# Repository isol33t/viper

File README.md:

# Duck Viper v1 PCB - Open Source Upgrade

⚠️ **Work in Progress** - This project is currently under development

Inspired by [Automated keyboard PCB design with ergogen and kbplacer by adamws](https://adamws.github.io/keyboard-pcb-design-with-ergogen-and-kbplacer/) & its [dockerfile](https://github.com/adamws/kicad-kbplacer/blob/develop/examples/absolem-ergogen/Dockerfile).

<!-- 

 -->

## Overview

An open-source PCB design for the Duck Viper v1 keyboard with hardware upgrades. This project focuses on transparency and community collaboration while building upon existing open-source resources.

**Disclaimer:** I'm not an electrical engineer - this project represents my attempt at "putting the parts together" using available community resources, guides, and libraries. Community feedback and contributions are greatly appreciated!

(Planned *) Upgrades: 
- USB-C Connector
- ESD
- Separate Caps Lock LED
- - RGB Underglow *
- - Additional switches for Split HHKB Bottom Row *
- - MXLockLed *

## Design Philosophy

- **Open Source First**: All design files, schematics, and documentation will be freely available
- **Community Driven**: Built using existing open-source libraries and community knowledge
- **Transparency**: Design decisions and trade-offs documented for others to learn from

## Current Status

[Link to PDF](hardware/schematic.pdf)

### Design Questions (Help Needed!)

**1. QFN vs QFP Package Decision**
- **QFN Pros**: Required for split HHKB layout with IC positioned between Caps Lock and A (see Voyager60 reference)
- **QFN Cons**: Hand soldering difficulty increases prototype cost (~$20 per PCB for 5-unit orders with just an assembled QFN IC vs ~$10 for 5 PCBs ex. assembly)
- **QFP**: Easier to hand solder but may not fit desired layout constraints due to additional stabilizer requirements for split HHKB

QFN IC placement mock-up:

*If going QFN route, schematic verification help would be greatly appreciated!*

## Supported Layouts

kbplacer can use via for switch placement & requires via for collapsing a KLE layout

VIA spec https://www.caniusevia.com/docs/layouts#overview uses KLE raw, but not kle.com's raw json
VIA spec based on [wt60_d](https://github.com/the-via/keyboards/blob/9da730d66a00c3ca1b9b9ac7e7078fc221432501/v3/wilba_tech/wt60_d/wt60_d.json#L9)

```
python -m kbplacer.kle_serial -in -in kle/keyboard-layout-via-10u.json -inform KLE_VIA -out keyboard-layout-collapsed.json -outform KLE_RAW -collapse
```

- Forked [duck_viper](https://adamws.github.io/keyboard-pcbs/#duck-eagle_viper-v2-eagle_viper)

### Split HHKB, 10u

[KLE permalink](https://keyboard-layout-editor.com/##@@_x:2&c=%23777777%3B&=0,0&_c=%23cccccc%3B&=0,1&=0,2&=0,3&=0,4&=0,5&=0,6&=0,7&=0,8&=0,9&=0,10&=0,11&=0,12&_c=%23aaaaaa&w:2%3B&=0,13%0A%0A%0A0,0&_x:1.5&c=%23cccccc%3B&=0,13%0A%0A%0A0,1&=0,14%0A%0A%0A0,1%3B&@_x:2&c=%23aaaaaa&w:1.5%3B&=1,0&_c=%23cccccc%3B&=1,1&=1,2&=1,3&=1,4&=1,5&=1,6&=1,7&=1,8&=1,9&=1,10&=1,11&=1,12&_w:1.5%3B&=1,13%3B&@_c=%23aaaaaa&w:1.25%3B&=2,0%0A%0A%0A3,1&_x:0.75&w:1.75%3B&=2,0%0A%0A%0A3,0&_c=%23cccccc%3B&=2,1&=2,2&=2,3&=2,4&=2,5&=2,6&=2,7&=2,8&=2,9&=2,10&=2,11&_c=%23777777&w:2.25%3B&=2,12%3B&@_x:2&c=%23aaaaaa&w:2.25%3B&=3,1&_c=%23cccccc%3B&=3,2&=3,3&=3,4&=3,5&=3,6&=3,7&=3,8&=3,9&=3,10&=3,11&_c=%23aaaaaa&w:2.75%3B&=3,12%0A%0A%0A1,0&_x:0.75&w:1.75%3B&=3,12%0A%0A%0A1,1&=3,13%0A%0A%0A1,1%3B&@_x:2&w:1.5&d:true%3B&=4,0%0A%0A%0A2,0&=4,2%0A%0A%0A2,0&_w:1.5%3B&=4,3%0A%0A%0A2,0&_c=%23cccccc&w:7%3B&=4,7%0A%0A%0A2,0&_c=%23aaaaaa&w:1.5%3B&=4,11%0A%0A%0A2,0&=4,13%0A%0A%0A2,0&_w:1.5&d:true%3B&=4,14%0A%0A%0A2,0%3B&@_x:2&y:0.5&w:1.5&d:true%3B&=4,0%0A%0A%0A2,1&=4,2%0A%0A%0A2,1&_w:1.5%3B&=4,3%0A%0A%0A2,1&_c=%23cccccc&w:3%3B&=4,5%0A%0A%0A2,1&=4,7%0A%0A%0A2,1&_w:3%3B&=4,9%0A%0A%0A2,1&_c=%23aaaaaa&w:1.5%3B&=4,11%0A%0A%0A2,1&=4,13%0A%0A%0A2,1&_w:1.5&d:true%3B&=4,14%0A%0A%0A2,1%3B&@_x:2&w:1.5&d:true%3B&=4,0%0A%0A%0A2,2&=4,2%0A%0A%0A2,2&_c=%23cccccc&w:10%3B&=4,7%0A%0A%0A2,2&_c=%23aaaaaa%3B&=4,13%0A%0A%0A2,2&_w:1.5&d:true%3B&=4,14%0A%0A%0A2,2)

<details>
<summary>KLE Raw data, expanded</summary>
```
[{"x": 2, "c": "#777777"}, "0,0", {"c": "#cccccc"}, "0,1", "0,2", "0,3", "0,4", "0,5", "0,6", "0,7", "0,8", "0,9", "0,10", "0,11", "0,12", {"c": "#aaaaaa", "w": 2}, "0,13\n\n\n0,0", {"x": 1.5, "c": "#cccccc"}, "0,13\n\n\n0,1", "0,14\n\n\n0,1"],
[{"x": 2, "c": "#aaaaaa", "w": 1.5}, "1,0", {"c": "#cccccc"}, "1,1", "1,2", "1,3", "1,4", "1,5", "1,6", "1,7", "1,8", "1,9", "1,10", "1,11", "1,12", {"w": 1.5}, "1,13"],
[{"c": "#aaaaaa", "w": 1.25}, "2,0\n\n\n3,1", {"x": 0.75, "w": 1.75}, "2,0\n\n\n3,0", {"c": "#cccccc"}, "2,1", "2,2", "2,3", "2,4", "2,5", "2,6", "2,7", "2,8", "2,9", "2,10", "2,11", {"c": "#777777", "w": 2.25}, "2,12"],
[{"x": 2, "c": "#aaaaaa", "w": 2.25}, "3,1", {"c": "#cccccc"}, "3,2", "3,3", "3,4", "3,5", "3,6", "3,7", "3,8", "3,9", "3,10", "3,11", {"c": "#aaaaaa", "w": 2.75}, "3,12\n\n\n1,0", {"x": 0.75, "w": 1.75}, "3,12\n\n\n1,1", "3,13\n\n\n1,1"],
[{"x": 2, "w": 1.5, "d": true}, "4,0\n\n\n2,0", "4,2\n\n\n2,0", {"w": 1.5}, "4,3\n\n\n2,0", {"c": "#cccccc", "w": 7}, "4,7\n\n\n2,0", {"c": "#aaaaaa", "w": 1.5}, "4,11\n\n\n2,0", "4,13\n\n\n2,0", {"w": 1.5, "d": true}, "4,14\n\n\n2,0"],
[{"x": 2, "y": 0.5, "w": 1.5, "d": true}, "4,0\n\n\n2,1", "4,2\n\n\n2,1", {"w": 1.5}, "4,3\n\n\n2,1", {"c": "#cccccc", "w": 3}, "4,5\n\n\n2,1", "4,7\n\n\n2,1", {"w": 3}, "4,9\n\n\n2,1", {"c": "#aaaaaa", "w": 1.5}, "4,11\n\n\n2,1", "4,13\n\n\n2,1", {"w": 1.5, "d": true}, "4,14\n\n\n2,1"],
[{"x": 2, "w": 1.5, "d": true}, "4,0\n\n\n2,2", "4,2\n\n\n2,2", {"c": "#cccccc", "w": 10}, "4,7\n\n\n2,2", {"c": "#aaaaaa"}, "4,13\n\n\n2,2", {"w": 1.5, "d": true}, "4,14\n\n\n2,2"]
```
</details>

[KLE permalink](https://keyboard-layout-editor.com/##@@_x:2&c=%23777777%3B&=0,0&_c=%23cccccc%3B&=0,1&=0,2&=0,3&=0,4&=0,5&=0,6&=0,7&=0,8&=0,9&=0,10&=0,11&=0,12&_c=%23aaaaaa&w:2%3B&=0,13%0A%0A%0A0,0&_x:-2&c=%23cccccc%3B&=0,13%0A%0A%0A0,1&=0,14%0A%0A%0A0,1%3B&@_x:2&c=%23aaaaaa&w:1.5%3B&=1,0&_c=%23cccccc%3B&=1,1&=1,2&=1,3&=1,4&=1,5&=1,6&=1,7&=1,8&=1,9&=1,10&=1,11&=1,12&_w:1.5%3B&=1,13%3B&@_x:2&c=%23aaaaaa&w:1.75%3B&=2,0%0A%0A%0A3,0&_x:-1.75&w:1.25%3B&=2,0%0A%0A%0A3,1&_x:0.5&c=%23cccccc%3B&=2,1&=2,2&=2,3&=2,4&=2,5&=2,6&=2,7&=2,8&=2,9&=2,10&=2,11&_c=%23777777&w:2.25%3B&=2,12%3B&@_x:2&c=%23aaaaaa&w:2.25%3B&=3,1&_c=%23cccccc%3B&=3,2&=3,3&=3,4&=3,5&=3,6&=3,7&=3,8&=3,9&=3,10&=3,11&_c=%23aaaaaa&w:2.75%3B&=3,12%0A%0A%0A1,0&_x:-2.75&w:1.75%3B&=3,12%0A%0A%0A1,1&=3,13%0A%0A%0A1,1%3B&@_x:3.5%3B&=4,2%0A%0A%0A2,0&_w:1.5%3B&=4,3%0A%0A%0A2,0&_c=%23cccccc&w:3%3B&=4,5%0A%0A%0A2,1&_x:-3&w:7%3B&=4,7%0A%0A%0A2,0&_x:-3&w:3%3B&=4,9%0A%0A%0A2,1&_c=%23aaaaaa&w:1.5%3B&=4,11%0A%0A%0A2,0&=4,13%0A%0A%0A2,0)

<details>
<summary>KLE Raw data, collapsed</summary>
```
[{"x": 2, "c": "#777777"}, "0,0", {"c": "#cccccc"}, "0,1", "0,2", "0,3", "0,4", "0,5", "0,6", "0,7", "0,8", "0,9", "0,10", "0,11", "0,12", {"c": "#aaaaaa", "w": 2}, "0,13\n\n\n0,0", {"x": -2, "c": "#cccccc"}, "0,13\n\n\n0,1", "0,14\n\n\n0,1"],
[{"x": 2, "c": "#aaaaaa", "w": 1.5}, "1,0", {"c": "#cccccc"}, "1,1", "1,2", "1,3", "1,4", "1,5", "1,6", "1,7", "1,8", "1,9", "1,10", "1,11", "1,12", {"w": 1.5}, "1,13"],
[{"x": 2.0, "c": "#aaaaaa", "w": 1.75}, "2,0\n\n\n3,0", {"x": -1.75, "w": 1.25}, "2,0\n\n\n3,1", {"x": 0.5, "c": "#cccccc"}, "2,1", "2,2", "2,3", "2,4", "2,5", "2,6", "2,7", "2,8", "2,9", "2,10", "2,11", {"c": "#777777", "w": 2.25}, "2,12"],
[{"x": 2, "c": "#aaaaaa", "w": 2.25}, "3,1", {"c": "#cccccc"}, "3,2", "3,3", "3,4", "3,5", "3,6", "3,7", "3,8", "3,9", "3,10", "3,11", {"c": "#aaaaaa", "w": 2.75}, "3,12\n\n\n1,0", {"x": -2.75, "w": 1.75}, "3,12\n\n\n1,1", "3,13\n\n\n1,1"],
[{"x": 3.5}, "4,2\n\n\n2,0", {"w": 1.5}, "4,3\n\n\n2,0", {"c": "#cccccc", "w": 3}, "4,5\n\n\n2,1", {"x": -3.0, "w": 7}, "4,7\n\n\n2,0", {"x": -3.0, "w": 3}, "4,9\n\n\n2,1", {"c": "#aaaaaa", "w": 1.5}, "4,11\n\n\n2,0", "4,13\n\n\n2,0"]
```
</details>

## Development Environment Setup

### Hardware Design (KiCad)

**Requirements:**
- KiCad 9.0 or later
- Git for version control
- - python3
- - docker

**Setup:**
```bash
# Clone the repository
git clone [repository-url]
cd duck-viper-v1-pcb

# Open the project in KiCad
# File -> Open Project -> duck-viper-v1.kicad_pro
```

**Setup for adamws/kbplacer:**
```bash
# Clone the repository
git clone [repository-url]
cd duck-viper-v1-pcb
python3 -m venv .venv
source .venv/bin/activate
python3 -m pip install .

python -m kbplacer.kle_serial -in kle/keyboard-layout-via.json -inform KLE_VIA -out kle/keyboard-layout-collapsed.json -outform KLE_INTERNAL -collapse
python tools/layout2url.py -in keyboard-layout-collapsed.json|pbcopy

# Open the project in KiCad
# File -> Open Project -> duck-viper-v1.kicad_pro
```

**linux**
```bash
python3 -m venv .venv --system-site-packages
source .venv/bin/activate
pip install .

# test kicad
python -c "import pcbnew; print(pcbnew.Version())"
```

**Libraries Used:**
- [AcheronProject/AlexandriaLibrary](https://github.com/AcheronProject/AlexandriaLibrary)
- Community keyboard libraries (specific sources TBD)

### Firmware Development

*Detailed firmware setup instructions will be added as development progresses.*

### Manufacturing Files

Generation of Gerber files, pick-and-place files, and BOM will be documented once design is finalized.

## Acknowledgments

This project builds upon the incredible work of the open-source keyboard community. Specific libraries, guides, and resources used will be documented as the project progresses.

## Contributing

As a learning project, I welcome:
- Schematic reviews and feedback
- Design suggestions and improvements
- Documentation contributions
- Testing and validation help

## Thanks yo

This project is inspired by [Automated Keyboard PCB design with ergogen and kbplacer](https://github.com/adamws/kicad-kbplacer/tree/master/examples/absolem-ergogen). Still, it's far from being fully automated.

- adamws/kicad-kbplacer
- https://github.com/ruiqimao/keyboard-pcb-guide
- https://wiki.ai03.com/books/pcb-design
- https://github.com/evyd13/plain60-b
- https://github.com/evyd13/plain60-c
- https://www.masterzen.fr/2020/05/03/designing-a-keyboard-part-1/

## License

[MIT](LICENSE)

---

*This project is a learning exercise in PCB design. Use at your own risk and always verify designs before manufacturing.*

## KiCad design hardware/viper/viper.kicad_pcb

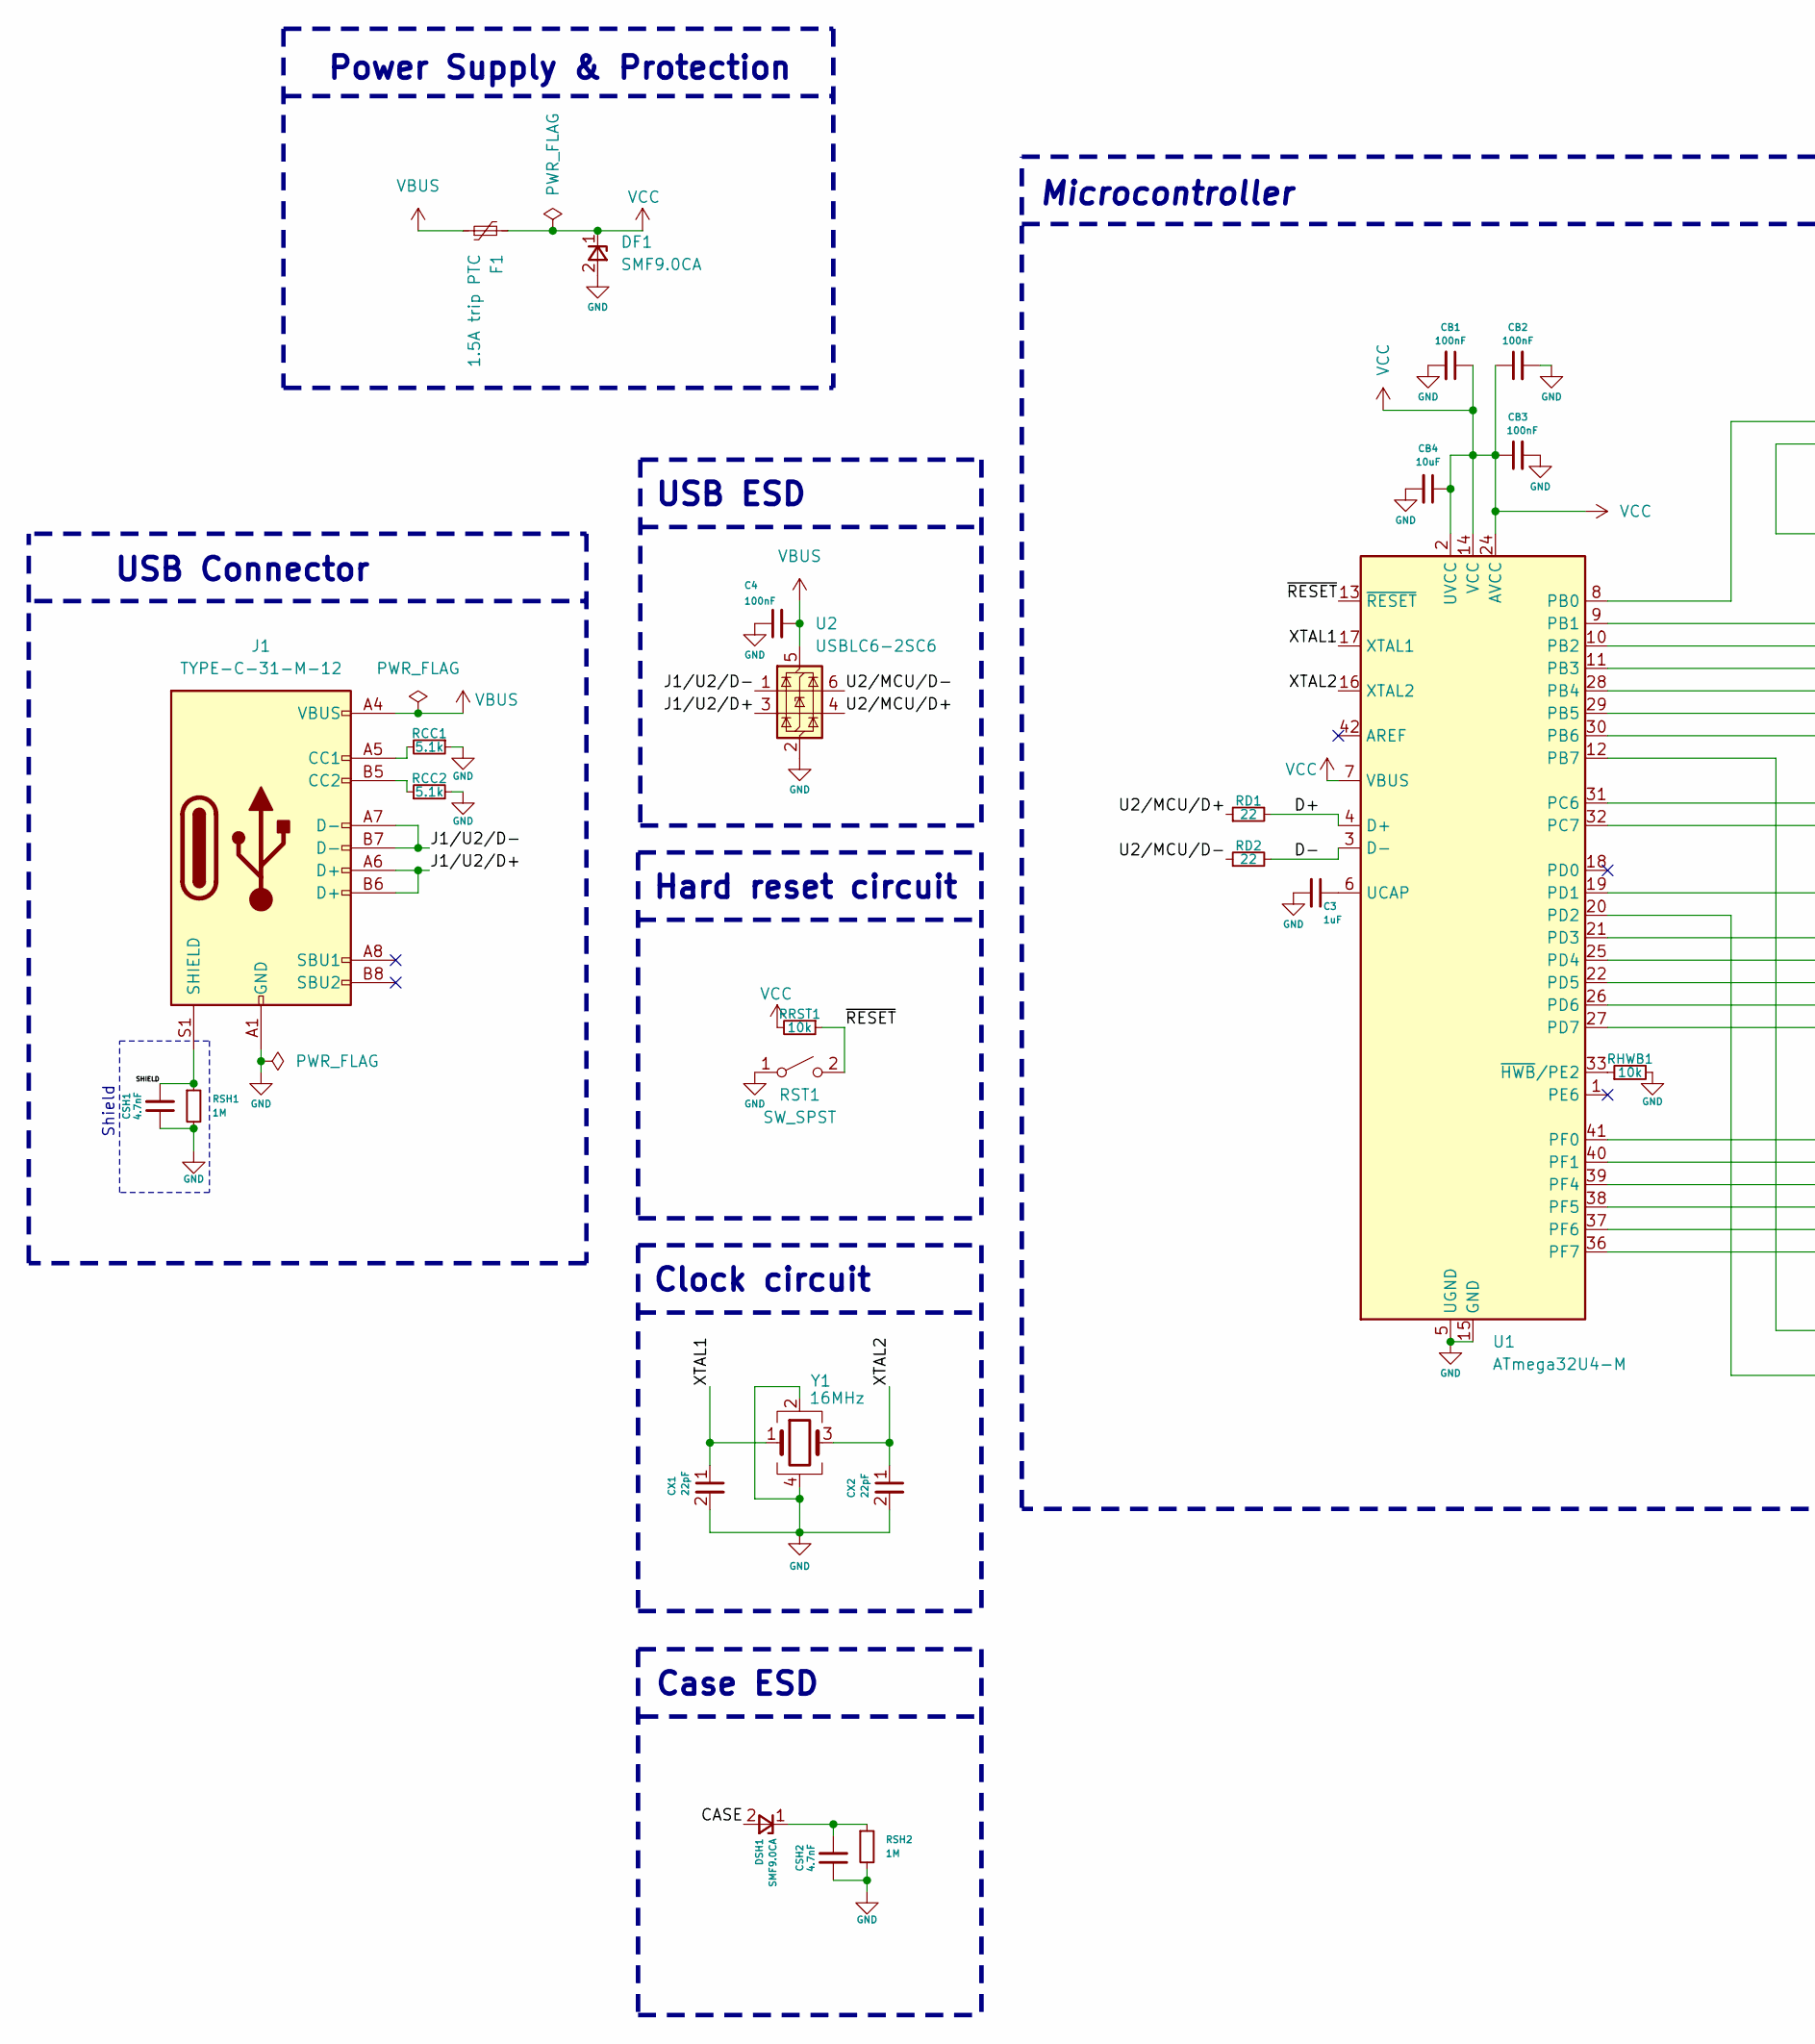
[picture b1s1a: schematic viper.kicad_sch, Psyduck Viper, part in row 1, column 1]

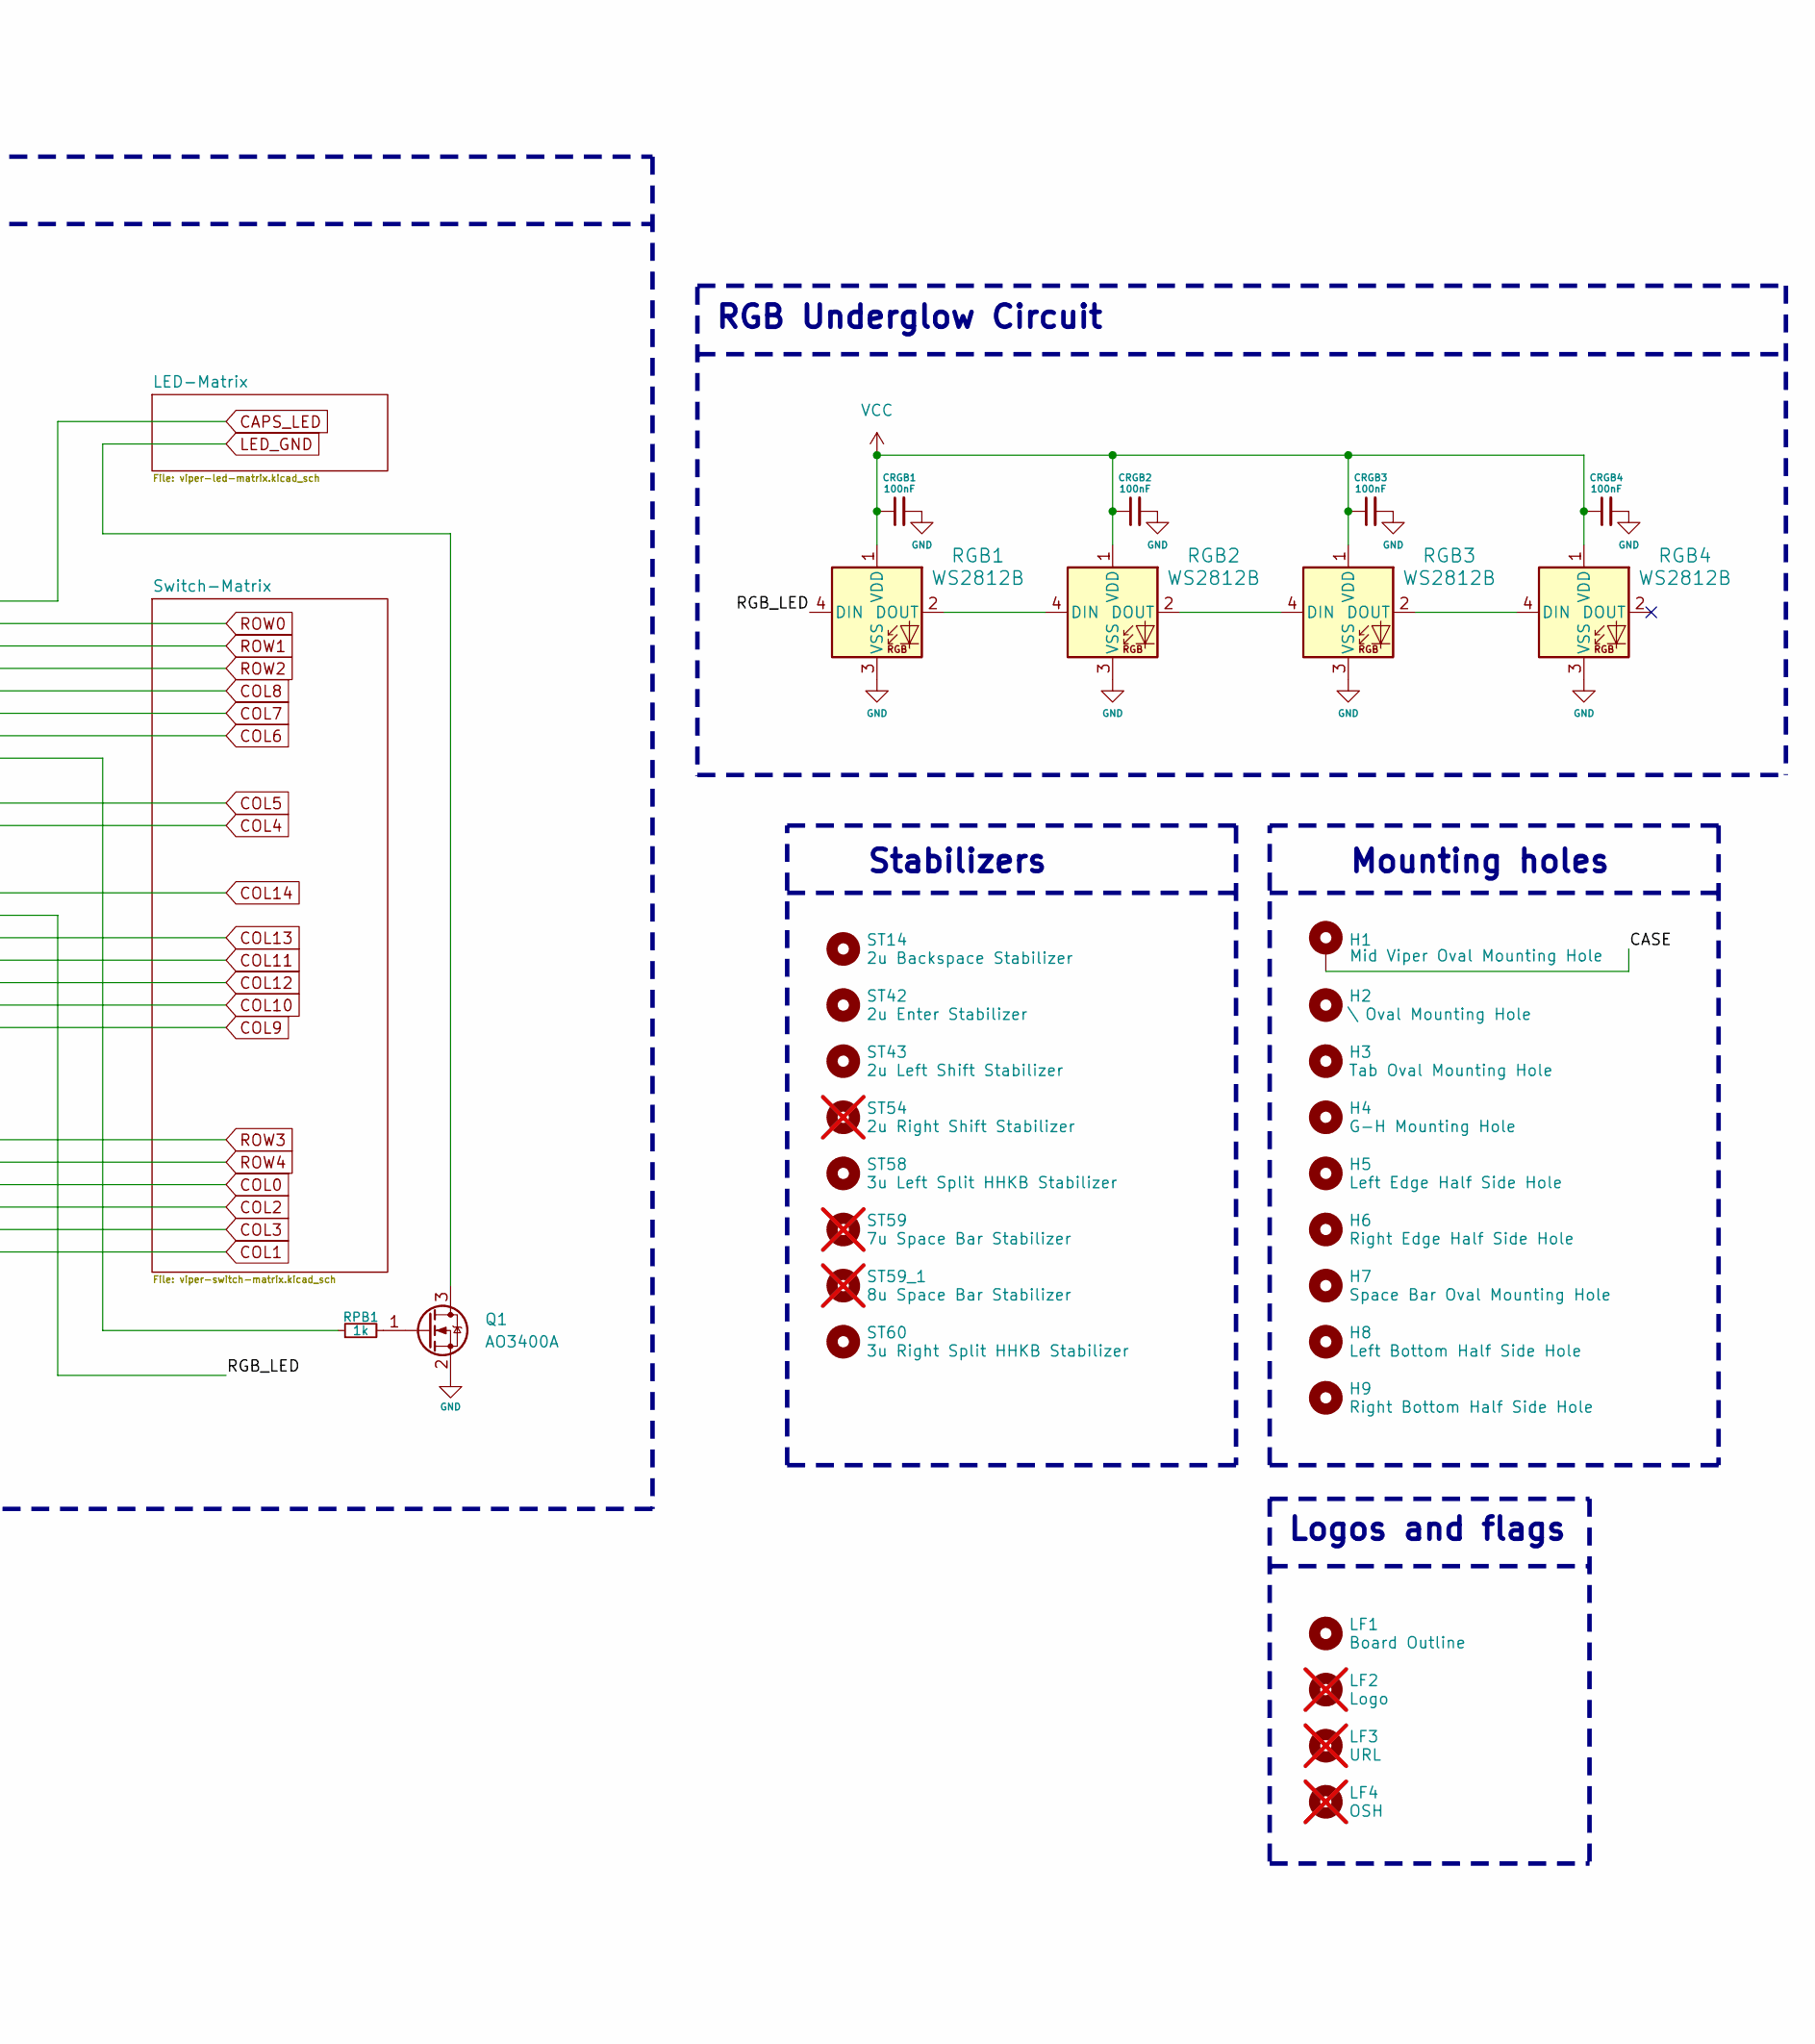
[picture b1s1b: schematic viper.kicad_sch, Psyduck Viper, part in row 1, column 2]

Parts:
C3: 1uF; C_0603_1608Metric; LCSC C29936
C4: 100nF; C_0805_2012Metric; LCSC C36911366
CB1, CB2, CB3: 100nF; C_0603_1608Metric; LCSC C1591
CB4: 10uF; C_0603_1608Metric; LCSC C96446
CRGB1, CRGB2, CRGB3, CRGB4: 100nF; C_0805_2012Metric; LCSC C36911366
CSH1, CSH2: 4.7nF; C_0805_2012Metric; LCSC C77063
CX1, CX2: 22pF; C_0603_1608Metric; LCSC C1653
DF1: SMF9.0CA; D_SOD-123; LCSC C19077504
DSH1: SMF9.0CA; D_SOD-123; LCSC C19077504
F1: 1.5A trip PTC; Fuse_1206_3216Metric; LCSC C2153712
H1: Mounting_Hole_Oval_2.5x8mm
H2, H3, H4, H7: MoutingHole_Oval_BackOnly_7mm_5.0x2.5mm
H5, H6, H8, H9: halfSideHole
J1: TYPE-C-31-M-12; USB_C_Receptacle_HRO_TYPE-C-31-M-12; LCSC C165948
LF1: viper_outline
LF2, LF3, LF4: not fitted
Q1: AO3400A; SOT-23; LCSC C7603192
RCC1, RCC2: 5.1k; R_0603_1608Metric; LCSC C23186
RD1, RD2: 22; R_0603_1608Metric; LCSC C23345
RGB1, RGB3, RGB4: WS2812B; LED_WS2812B-Mini_PLCC4_3.5x3.5mm; LCSC C5349955
RGB2: WS2812B; LED_WS2812B-Mini_PLCC4_3.5x3.5mm; LCSC C527089
RHWB1: 10k; R_0603_1608Metric; LCSC C25804
RPB1: 1k; R_0805_2012Metric; LCSC C17513
RRST1: 10k; R_0603_1608Metric; LCSC C25804
RSH1, RSH2: 1M; R_0805_2012Metric
RST1: SW_SPST; SW_SPST_TL3342; LCSC C92584
ST14, ST42, ST43: Stabilizer_Cherry_MX_2.00u
ST54: Stabilizer_Cherry_MX_2.00u; not fitted
ST58, ST60: Stabilizer_Cherry_MX_3.00u
ST59: Stabilizer_Cherry_MX_7.00u; not fitted
ST59_1: Stabilizer_Cherry_MX_8.00u; not fitted
U1: ATmega32U4-M; QFN-44-1EP_7x7mm_P0.5mm_EP5.2x5.2mm; LCSC C112161
U2: USBLC6-2SC6; SOT-23-6; LCSC C7519
Y1: 16MHz; Crystal_SMD_3225-4Pin_3.2x2.5mm; LCSC C255909

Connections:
/CASE: DSH1.2 (A), H1.1
/D+: RD1.2, U1.4 (D+)
/D-: RD2.2, U1.3 (D-)
/J1/U2/D+: J1.A6 (D+), J1.B6 (D+), U2.3 (I/O2)
/J1/U2/D-: J1.A7 (D-), J1.B7 (D-), U2.1 (I/O1)
/RGB_LED: RGB1.4 (DIN), U1.20 (PD2)
/SHIELD: CSH1.2, J1.S1 (SHIELD), RSH1.1
/U2/MCU/D+: RD1.1, U2.4 (I/O2)
/U2/MCU/D-: RD2.1, U2.6 (I/O1)
/XTAL1: CX1.1, U1.17 (XTAL1), Y1.1
/XTAL2: CX2.1, U1.16 (XTAL2), Y1.3
/~RESET: RRST1.1, RST1.2 (B), U1.13 (~RESET)
CAPS_LED: U1.8 (PB0); also elsewhere on the board
COL0: U1.39 (PF4); also elsewhere on the board
COL1: U1.36 (PF7); also elsewhere on the board
COL2: U1.38 (PF5); also elsewhere on the board
COL3: U1.37 (PF6); also elsewhere on the board
COL4: U1.32 (PC7); also elsewhere on the board
COL5: U1.31 (PC6); also elsewhere on the board
COL6: U1.30 (PB6); also elsewhere on the board
COL7: U1.29 (PB5); also elsewhere on the board
COL8: U1.28 (PB4); also elsewhere on the board
COL9: U1.27 (PD7); also elsewhere on the board
COL10: U1.26 (PD6); also elsewhere on the board
COL11: U1.25 (PD4); also elsewhere on the board
COL12: U1.22 (PD5); also elsewhere on the board
COL13: U1.21 (PD3); also elsewhere on the board
COL14: U1.19 (PD1); also elsewhere on the board
GND: C3.2, C4.1, CB1.2, CB2.2, CB3.2, CB4.2, CRGB1.2, CRGB2.2, CRGB3.2, CRGB4.2, CSH1.1, CSH2.1, CX1.2, CX2.2, DF1.2 (A), J1.A1 (GND), J1.A12 (GND), J1.B1 (GND), J1.B12 (GND), Q1.2 (S), RCC1.1, RCC2.2, RGB1.3 (VSS), RGB2.3 (VSS), RGB3.3 (VSS), RGB4.3 (VSS), RHWB1.2, RSH1.2, RSH2.2, RST1.1 (A), U1.5 (UGND), U1.15 (GND), U1.23 (GND), U1.35 (GND), U1.43 (GND), U1.45 (GND), U2.2 (GND), Y1.2, Y1.4
LED_GND: Q1.3 (D); also elsewhere on the board
unnamed: CSH2.2, DSH1.1 (K), RSH2.1
unnamed: J1.A5 (CC1), RCC1.2
unnamed: J1.B5 (CC2), RCC2.1
unnamed: Q1.1 (G), RPB1.2
unnamed: RGB1.2 (DOUT), RGB2.4 (DIN)
unnamed: RGB2.2 (DOUT), RGB3.4 (DIN)
unnamed: RGB3.2 (DOUT), RGB4.4 (DIN)
unnamed: RPB1.1, U1.12 (PB7)
unnamed: C3.1, U1.6 (UCAP)
unnamed: RHWB1.1, U1.33 (~HWB/PE2)
ROW0: U1.9 (PB1); also elsewhere on the board
ROW1: U1.10 (PB2); also elsewhere on the board
ROW2: U1.11 (PB3); also elsewhere on the board
ROW3: U1.41 (PF0); also elsewhere on the board
ROW4: U1.40 (PF1); also elsewhere on the board
VBUS: C4.2, F1.1, J1.A4 (VBUS), J1.A9 (VBUS), J1.B4 (VBUS), J1.B9 (VBUS), U2.5 (VBUS)
VCC: CB1.1, CB2.1, CB3.1, CB4.1, CRGB1.1, CRGB2.1, CRGB3.1, CRGB4.1, DF1.1 (K), F1.2, RGB1.1 (VDD), RGB2.1 (VDD), RGB3.1 (VDD), RGB4.1 (VDD), RRST1.2, U1.2 (UVCC), U1.7 (VBUS), U1.14 (VCC), U1.24 (AVCC), U1.34 (VCC), U1.44 (AVCC); also elsewhere on the board

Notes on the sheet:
Power Supply & Protection
Shield
Clock circuit
RGB Underglow Circuit
USB ESD
Hard reset circuit
USB Connector
Logos and flags
Microcontroller
Mounting holes
Case ESD
Stabilizers

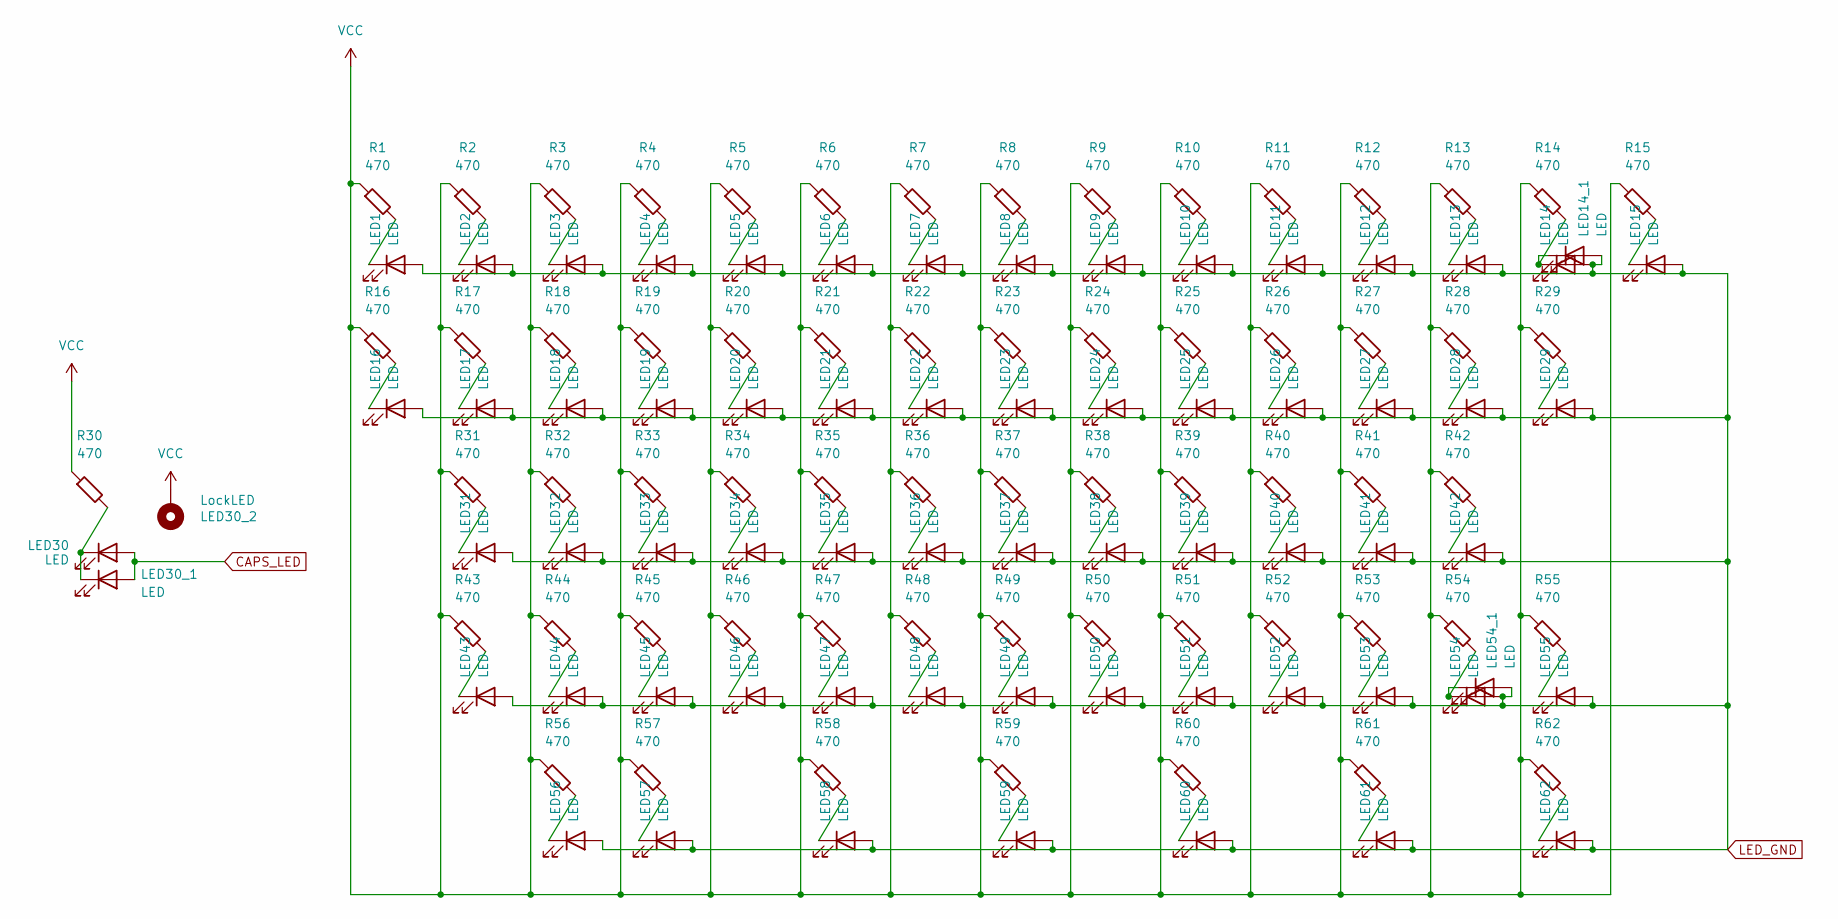
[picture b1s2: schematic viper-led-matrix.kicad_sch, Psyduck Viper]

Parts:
LED1, LED2, LED3, LED4, LED5, LED6, LED7, LED8, LED9, LED10, LED11, LED12, LED13, LED14, LED14_1, LED15, LED16, LED17, LED18, LED19, LED20, LED21, LED22, LED23, LED24, LED25, LED26, LED27, LED28, LED29, LED30, LED30_1, LED31, LED32, LED33, LED34, LED35, LED36, LED37, LED38, LED39, LED40, LED41, LED42, LED43, LED44, LED45, LED46, LED47, LED48, LED49, LED50, LED51, LED52, LED53, LED54, LED54_1, LED55, LED56, LED57, LED58, LED59, LED60, LED61, LED62: LED; MX-LED; LCSC C5440555
LED30_2: LockLED; MX-Lock-LED; LCSC C5440555
R1, R2, R3, R4, R5, R6, R7, R8, R9, R10, R11, R12, R13, R14, R15, R16, R17, R18, R19, R20, R21, R22, R23, R24, R25, R26, R27, R28, R29, R30, R31, R32, R33, R34, R35, R36, R37, R38, R39, R40, R41, R42, R43, R44, R45, R46, R47, R48, R49, R50, R51, R52, R53, R54, R55, R56, R57, R58, R59, R60, R61, R62: 470; R_0805_2012Metric; LCSC C17710

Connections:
CAPS_LED: LED30.2 (A), LED30_1.2 (A); also elsewhere on the board
LED_GND: LED1.2 (A), LED2.2 (A), LED3.2 (A), LED4.2 (A), LED5.2 (A), LED6.2 (A), LED7.2 (A), LED8.2 (A), LED9.2 (A), LED10.2 (A), LED11.2 (A), LED12.2 (A), LED13.2 (A), LED14.2 (A), LED14_1.2 (A), LED15.2 (A), LED16.2 (A), LED17.2 (A), LED18.2 (A), LED19.2 (A), LED20.2 (A), LED21.2 (A), LED22.2 (A), LED23.2 (A), LED24.2 (A), LED25.2 (A), LED26.2 (A), LED27.2 (A), LED28.2 (A), LED29.2 (A), LED31.2 (A), LED32.2 (A), LED33.2 (A), LED34.2 (A), LED35.2 (A), LED36.2 (A), LED37.2 (A), LED38.2 (A), LED39.2 (A), LED40.2 (A), LED41.2 (A), LED42.2 (A), LED43.2 (A), LED44.2 (A), LED45.2 (A), LED46.2 (A), LED47.2 (A), LED48.2 (A), LED49.2 (A), LED50.2 (A), LED51.2 (A), LED52.2 (A), LED53.2 (A), LED54.2 (A), LED54_1.2 (A), LED55.2 (A), LED56.2 (A), LED57.2 (A), LED58.2 (A), LED59.2 (A), LED60.2 (A), LED61.2 (A), LED62.2 (A); also elsewhere on the board
unnamed: LED1.1 (K), R1.2
unnamed: LED2.1 (K), R2.2
unnamed: LED3.1 (K), R3.2
unnamed: LED4.1 (K), R4.2
unnamed: LED5.1 (K), R5.2
unnamed: LED6.1 (K), R6.2
unnamed: LED7.1 (K), R7.2
unnamed: LED8.1 (K), R8.2
unnamed: LED9.1 (K), R9.2
unnamed: LED10.1 (K), R10.2
unnamed: LED11.1 (K), R11.2
unnamed: LED12.1 (K), R12.2
unnamed: LED13.1 (K), R13.2
unnamed: LED14.1 (K), LED14_1.1 (K), R14.2
unnamed: LED15.1 (K), R15.2
unnamed: LED16.1 (K), R16.2
unnamed: LED17.1 (K), R17.2
unnamed: LED18.1 (K), R18.2
unnamed: LED19.1 (K), R19.2
unnamed: LED20.1 (K), R20.2
unnamed: LED21.1 (K), R21.2
unnamed: LED22.1 (K), R22.2
unnamed: LED23.1 (K), R23.2
unnamed: LED24.1 (K), R24.2
unnamed: LED25.1 (K), R25.2
unnamed: LED26.1 (K), R26.2
unnamed: LED27.1 (K), R27.2
unnamed: LED28.1 (K), R28.2
unnamed: LED29.1 (K), R29.2
unnamed: LED30.1 (K), LED30_1.1 (K), R30.2
unnamed: LED31.1 (K), R31.2
unnamed: LED32.1 (K), R32.2
unnamed: LED33.1 (K), R33.2
unnamed: LED34.1 (K), R34.2
unnamed: LED35.1 (K), R35.2
unnamed: LED36.1 (K), R36.2
unnamed: LED37.1 (K), R37.2
unnamed: LED38.1 (K), R38.2
unnamed: LED39.1 (K), R39.2
unnamed: LED40.1 (K), R40.2
unnamed: LED41.1 (K), R41.2
unnamed: LED42.1 (K), R42.2
unnamed: LED43.1 (K), R43.2
unnamed: LED44.1 (K), R44.2
unnamed: LED45.1 (K), R45.2
unnamed: LED46.1 (K), R46.2
unnamed: LED47.1 (K), R47.2
unnamed: LED48.1 (K), R48.2
unnamed: LED49.1 (K), R49.2
unnamed: LED50.1 (K), R50.2
unnamed: LED51.1 (K), R51.2
unnamed: LED52.1 (K), R52.2
unnamed: LED53.1 (K), R53.2
unnamed: LED54.1 (K), LED54_1.1 (K), R54.2
unnamed: LED55.1 (K), R55.2
unnamed: LED56.1 (K), R56.2
unnamed: LED57.1 (K), R57.2
unnamed: LED58.1 (K), R58.2
unnamed: LED59.1 (K), R59.2
unnamed: LED60.1 (K), R60.2
unnamed: LED61.1 (K), R61.2
unnamed: LED62.1 (K), R62.2
VCC: LED30_2.1, R1.1, R2.1, R3.1, R4.1, R5.1, R6.1, R7.1, R8.1, R9.1, R10.1, R11.1, R12.1, R13.1, R14.1, R15.1, R16.1, R17.1, R18.1, R19.1, R20.1, R21.1, R22.1, R23.1, R24.1, R25.1, R26.1, R27.1, R28.1, R29.1, R30.1, R31.1, R32.1, R33.1, R34.1, R35.1, R36.1, R37.1, R38.1, R39.1, R40.1, R41.1, R42.1, R43.1, R44.1, R45.1, R46.1, R47.1, R48.1, R49.1, R50.1, R51.1, R52.1, R53.1, R54.1, R55.1, R56.1, R57.1, R58.1, R59.1, R60.1, R61.1, R62.1; also elsewhere on the board

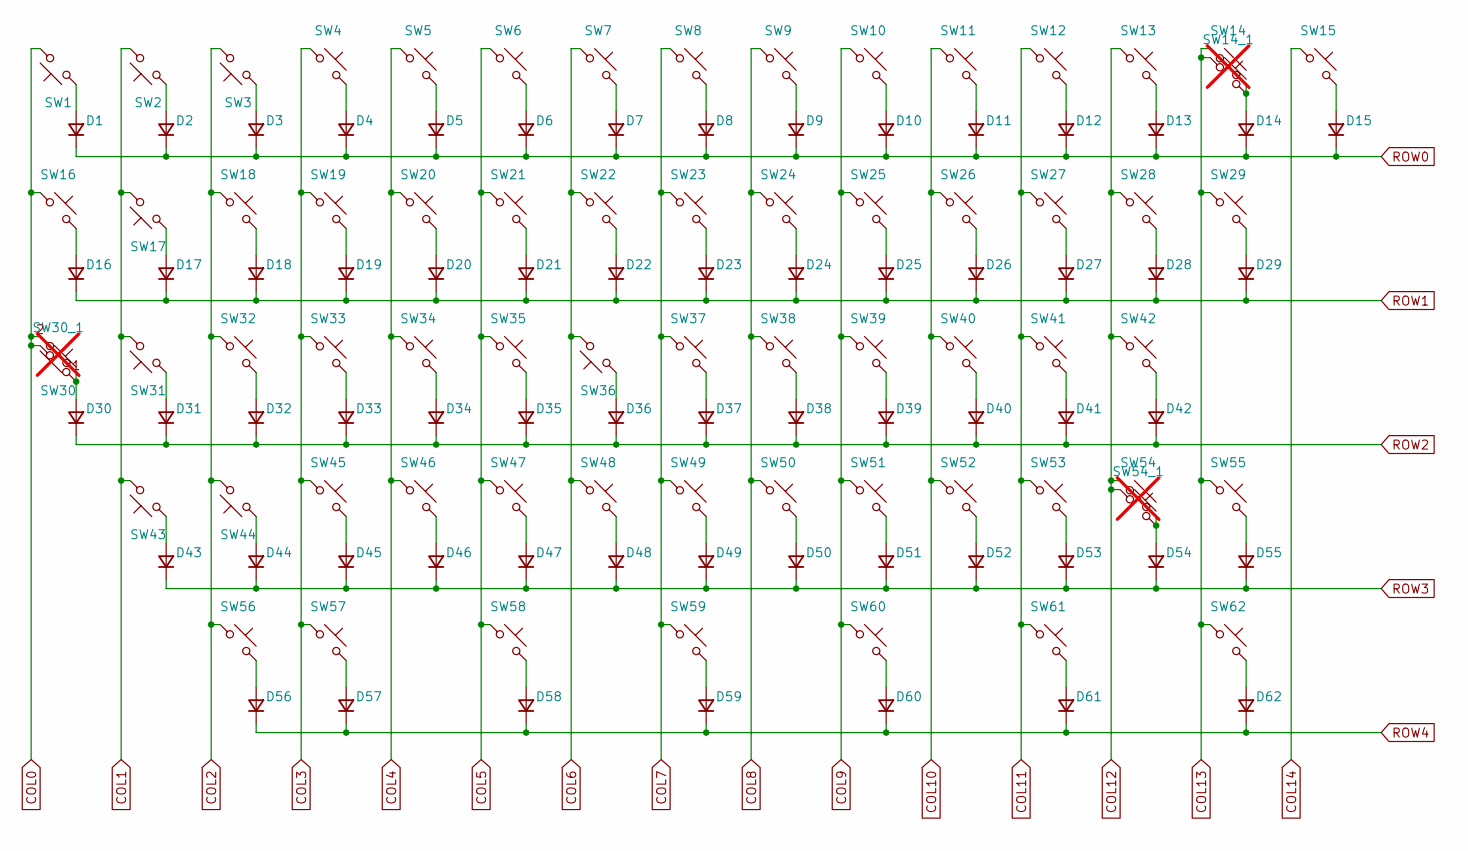
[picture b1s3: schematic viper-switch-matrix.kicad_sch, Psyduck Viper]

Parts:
D1, D2, D3, D4, D5, D6, D7, D8, D9, D10, D11, D12, D13, D14, D15, D16, D17, D18, D19, D20, D21, D22, D23, D24, D25, D26, D27, D28, D29, D30, D31, D32, D33, D34, D35, D36, D37, D38, D39, D40, D41, D42, D43, D44, D45, D46, D47, D48, D49, D50, D51, D52, D53, D54, D55, D56, D57, D58, D59, D60, D61, D62: 1N4148; D_0805_2012Metric; LCSC C109001
SW1, SW2, SW3, SW4, SW5, SW6, SW7, SW8, SW9, SW10, SW11, SW12, SW13, SW14_1, SW15, SW16, SW17, SW18, SW19, SW20, SW21, SW22, SW23, SW24, SW25, SW26, SW27, SW28, SW29, SW30_1, SW31, SW32, SW33, SW34, SW35, SW36, SW37, SW38, SW39, SW40, SW41, SW42, SW43, SW44, SW45, SW46, SW47, SW48, SW49, SW50, SW51, SW52, SW53, SW54_1, SW55, SW56, SW57, SW58, SW59, SW60, SW61, SW62: SW_Push; SW_Hybrid_Cherry_MX_Alps_1.00u_1
SW14, SW30, SW54: SW_Push; SW_Hybrid_Cherry_MX_Alps_1.00u_1; not fitted

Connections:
COL0: SW1.2, SW16.1, SW30.2, SW30_1.1; also elsewhere on the board
COL1: SW2.2, SW17.2, SW31.2, SW43.2; also elsewhere on the board
COL2: SW3.2, SW18.1, SW32.1, SW44.2, SW56.1; also elsewhere on the board
COL3: SW4.1, SW19.1, SW33.1, SW45.1, SW57.1; also elsewhere on the board
COL4: SW5.1, SW20.1, SW34.1, SW46.1; also elsewhere on the board
COL5: SW6.1, SW21.1, SW35.1, SW47.1, SW58.1; also elsewhere on the board
COL6: SW7.1, SW22.1, SW36.2, SW48.1; also elsewhere on the board
COL7: SW8.1, SW23.1, SW37.1, SW49.1, SW59.1; also elsewhere on the board
COL8: SW9.1, SW24.1, SW38.1, SW50.1; also elsewhere on the board
COL9: SW10.1, SW25.1, SW39.1, SW51.1, SW60.1; also elsewhere on the board
COL10: SW11.1, SW26.1, SW40.1, SW52.1; also elsewhere on the board
COL11: SW12.1, SW27.1, SW41.1, SW53.1, SW61.1; also elsewhere on the board
COL12: SW13.1, SW28.1, SW42.1, SW54.1, SW54_1.1; also elsewhere on the board
COL13: SW14.1, SW14_1.1, SW29.1, SW55.1, SW62.1; also elsewhere on the board
COL14: SW15.1; also elsewhere on the board
unnamed: D1.2 (A), SW1.1
unnamed: D2.2 (A), SW2.1
unnamed: D3.2 (A), SW3.1
unnamed: D4.2 (A), SW4.2
unnamed: D5.2 (A), SW5.2
unnamed: D6.2 (A), SW6.2
unnamed: D7.2 (A), SW7.2
unnamed: D8.2 (A), SW8.2
unnamed: D9.2 (A), SW9.2
unnamed: D10.2 (A), SW10.2
unnamed: D11.2 (A), SW11.2
unnamed: D12.2 (A), SW12.2
unnamed: D13.2 (A), SW13.2
unnamed: D14.2 (A), SW14.2, SW14_1.2
unnamed: D15.2 (A), SW15.2
unnamed: D16.2 (A), SW16.2
unnamed: D17.2 (A), SW17.1
unnamed: D18.2 (A), SW18.2
unnamed: D19.2 (A), SW19.2
unnamed: D20.2 (A), SW20.2
unnamed: D21.2 (A), SW21.2
unnamed: D22.2 (A), SW22.2
unnamed: D23.2 (A), SW23.2
unnamed: D24.2 (A), SW24.2
unnamed: D25.2 (A), SW25.2
unnamed: D26.2 (A), SW26.2
unnamed: D27.2 (A), SW27.2
unnamed: D28.2 (A), SW28.2
unnamed: D29.2 (A), SW29.2
unnamed: D30.2 (A), SW30.1, SW30_1.2
unnamed: D31.2 (A), SW31.1
unnamed: D32.2 (A), SW32.2
unnamed: D33.2 (A), SW33.2
unnamed: D34.2 (A), SW34.2
unnamed: D35.2 (A), SW35.2
unnamed: D36.2 (A), SW36.1
unnamed: D37.2 (A), SW37.2
unnamed: D38.2 (A), SW38.2
unnamed: D39.2 (A), SW39.2
unnamed: D40.2 (A), SW40.2
unnamed: D41.2 (A), SW41.2
unnamed: D42.2 (A), SW42.2
unnamed: D43.2 (A), SW43.1
unnamed: D44.2 (A), SW44.1
unnamed: D45.2 (A), SW45.2
unnamed: D46.2 (A), SW46.2
unnamed: D47.2 (A), SW47.2
unnamed: D48.2 (A), SW48.2
unnamed: D49.2 (A), SW49.2
unnamed: D50.2 (A), SW50.2
unnamed: D51.2 (A), SW51.2
unnamed: D52.2 (A), SW52.2
unnamed: D53.2 (A), SW53.2
unnamed: D54.2 (A), SW54.2, SW54_1.2
unnamed: D55.2 (A), SW55.2
unnamed: D56.2 (A), SW56.2
unnamed: D57.2 (A), SW57.2
unnamed: D58.2 (A), SW58.2
unnamed: D59.2 (A), SW59.2
unnamed: D60.2 (A), SW60.2
unnamed: D61.2 (A), SW61.2
unnamed: D62.2 (A), SW62.2
ROW0: D1.1 (K), D2.1 (K), D3.1 (K), D4.1 (K), D5.1 (K), D6.1 (K), D7.1 (K), D8.1 (K), D9.1 (K), D10.1 (K), D11.1 (K), D12.1 (K), D13.1 (K), D14.1 (K), D15.1 (K); also elsewhere on the board
ROW1: D16.1 (K), D17.1 (K), D18.1 (K), D19.1 (K), D20.1 (K), D21.1 (K), D22.1 (K), D23.1 (K), D24.1 (K), D25.1 (K), D26.1 (K), D27.1 (K), D28.1 (K), D29.1 (K); also elsewhere on the board
ROW2: D30.1 (K), D31.1 (K), D32.1 (K), D33.1 (K), D34.1 (K), D35.1 (K), D36.1 (K), D37.1 (K), D38.1 (K), D39.1 (K), D40.1 (K), D41.1 (K), D42.1 (K); also elsewhere on the board
ROW3: D43.1 (K), D44.1 (K), D45.1 (K), D46.1 (K), D47.1 (K), D48.1 (K), D49.1 (K), D50.1 (K), D51.1 (K), D52.1 (K), D53.1 (K), D54.1 (K), D55.1 (K); also elsewhere on the board
ROW4: D56.1 (K), D57.1 (K), D58.1 (K), D59.1 (K), D60.1 (K), D61.1 (K), D62.1 (K); also elsewhere on the board
